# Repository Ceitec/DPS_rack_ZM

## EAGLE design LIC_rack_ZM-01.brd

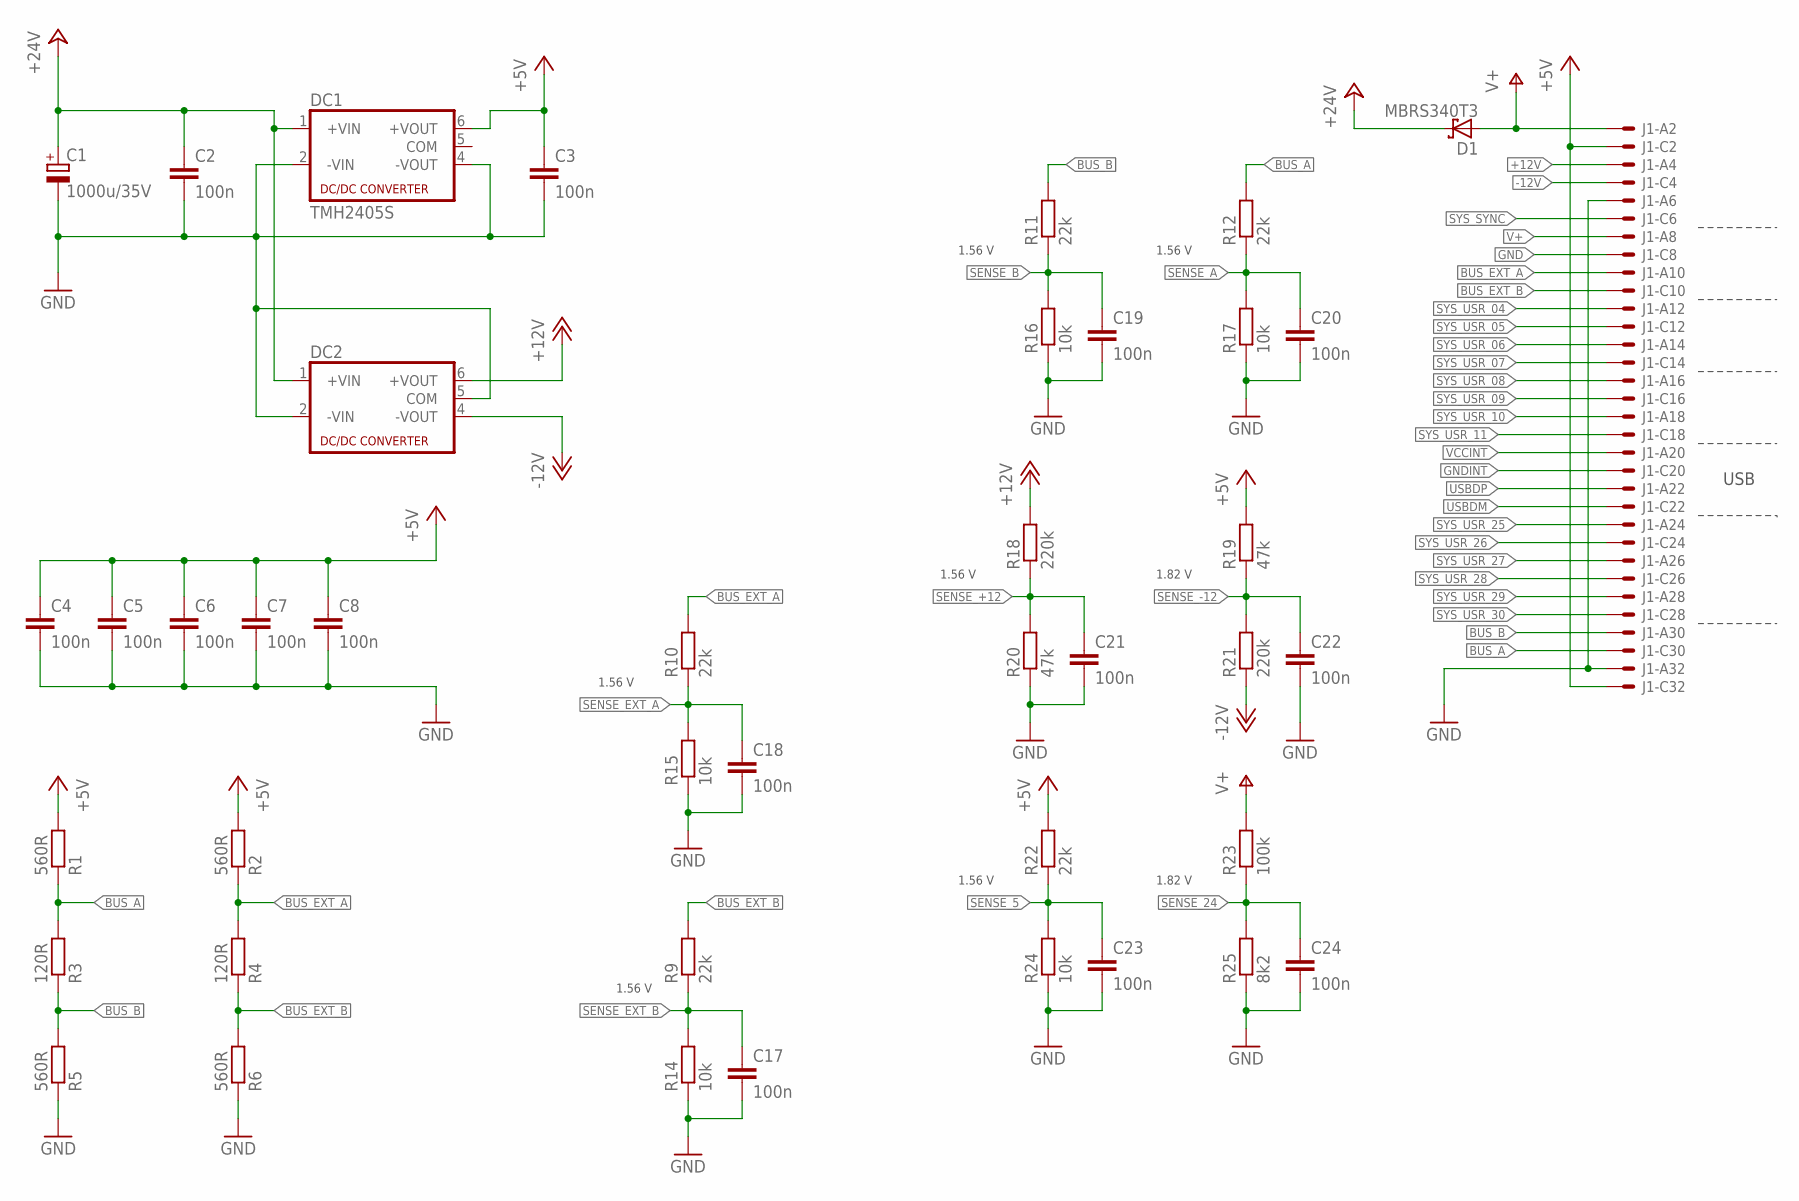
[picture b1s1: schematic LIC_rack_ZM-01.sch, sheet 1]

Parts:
C1: 1000u/35V; E5-13X26-LR
C2, C3, C4, C5, C6, C7, C8, C17, C18, C19, C20, C21, C22, C23, C24: 100n; C1206
D1: MBRS340T3; SMC
DC1: TMH2405S; NMA
DC2: NMA
J1: VG32SP; VG32P
R1, R2, R5, R6: 560R; R1206
R3, R4: 120R; R1206
R9, R10, R11, R12, R22: 22k; R1206
R14, R15, R16, R17, R24: 10k; R1206
R18, R21: 220k; R1206
R19, R20: 47k; R1206
R23: 100k; R1206
R25: 8k2; R1206

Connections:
+5V: C3.1, C4.1, C5.1, C6.1, C7.1, C8.1, DC1.6 (+VOUT), J1.C2 (MS), J1.C32 (MSV), R1.2, R2.2, R19.2, R22.2; also elsewhere on the board
+12V: DC2.6 (+VOUT), J1.A4 (MS), R18.2
+24V: C1.+, C2.1, D1.C, DC1.1 (+VIN), DC2.1 (+VIN)
-12V: DC2.4 (-VOUT), J1.C4 (MS), R21.1
BUS_A: J1.C30 (MS), R1.1, R3.2, R12.2; also elsewhere on the board
BUS_B: J1.A30 (MS), R3.1, R5.2, R11.2; also elsewhere on the board
BUS_EXT_A: J1.A10 (MS), R2.1, R4.2, R10.2; also elsewhere on the board
BUS_EXT_B: J1.C10 (MS), R4.1, R6.2, R9.2; also elsewhere on the board
GND: C1.-, C2.2, C3.2, C4.2, C5.2, C6.2, C7.2, C8.2, C17.2, C18.2, C19.2, C20.2, C21.2, C22.2, C23.2, C24.2, DC1.2 (-VIN), DC1.4 (-VOUT), DC2.2 (-VIN), DC2.5 (COM), J1.A6 (MS), J1.A32 (MS), J1.C8 (MS), R5.1, R6.1, R14.1, R15.1, R16.1, R17.1, R20.1, R24.1, R25.1; also elsewhere on the board
GNDINT: J1.C20 (MS); also elsewhere on the board
SENSE_5: C23.1, R22.1, R24.2; also elsewhere on the board
SENSE_24: C24.1, R23.1, R25.2; also elsewhere on the board
SENSE_+12: C21.1, R18.1, R20.2; also elsewhere on the board
SENSE_-12: C22.1, R19.1, R21.2; also elsewhere on the board
SENSE_A: C20.1, R12.1, R17.2; also elsewhere on the board
SENSE_B: C19.1, R11.1, R16.2; also elsewhere on the board
SENSE_EXT_A: C18.1, R10.1, R15.2; also elsewhere on the board
SENSE_EXT_B: C17.1, R9.1, R14.2; also elsewhere on the board
SYS_SYNC: J1.C6 (MS)
SYS_USR_04: J1.A12 (MS)
SYS_USR_05: J1.C12 (MS)
SYS_USR_06: J1.A14 (MS)
SYS_USR_07: J1.C14 (MS)
SYS_USR_08: J1.A16 (MS)
SYS_USR_09: J1.C16 (MS)
SYS_USR_10: J1.A18 (MS)
SYS_USR_11: J1.C18 (MS)
SYS_USR_25: J1.A24 (MS)
SYS_USR_26: J1.C24 (MS)
SYS_USR_27: J1.A26 (MS)
SYS_USR_28: J1.C26 (MS)
SYS_USR_29: J1.A28 (MS)
SYS_USR_30: J1.C28 (MS)
USBDM: J1.C22 (MS); also elsewhere on the board
USBDP: J1.A22 (MS); also elsewhere on the board
V+: D1.A, J1.A2 (MS), J1.A8 (MS), R23.2
VCCINT: J1.A20 (MS); also elsewhere on the board

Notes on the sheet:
1.82 V
1.56 V
USB

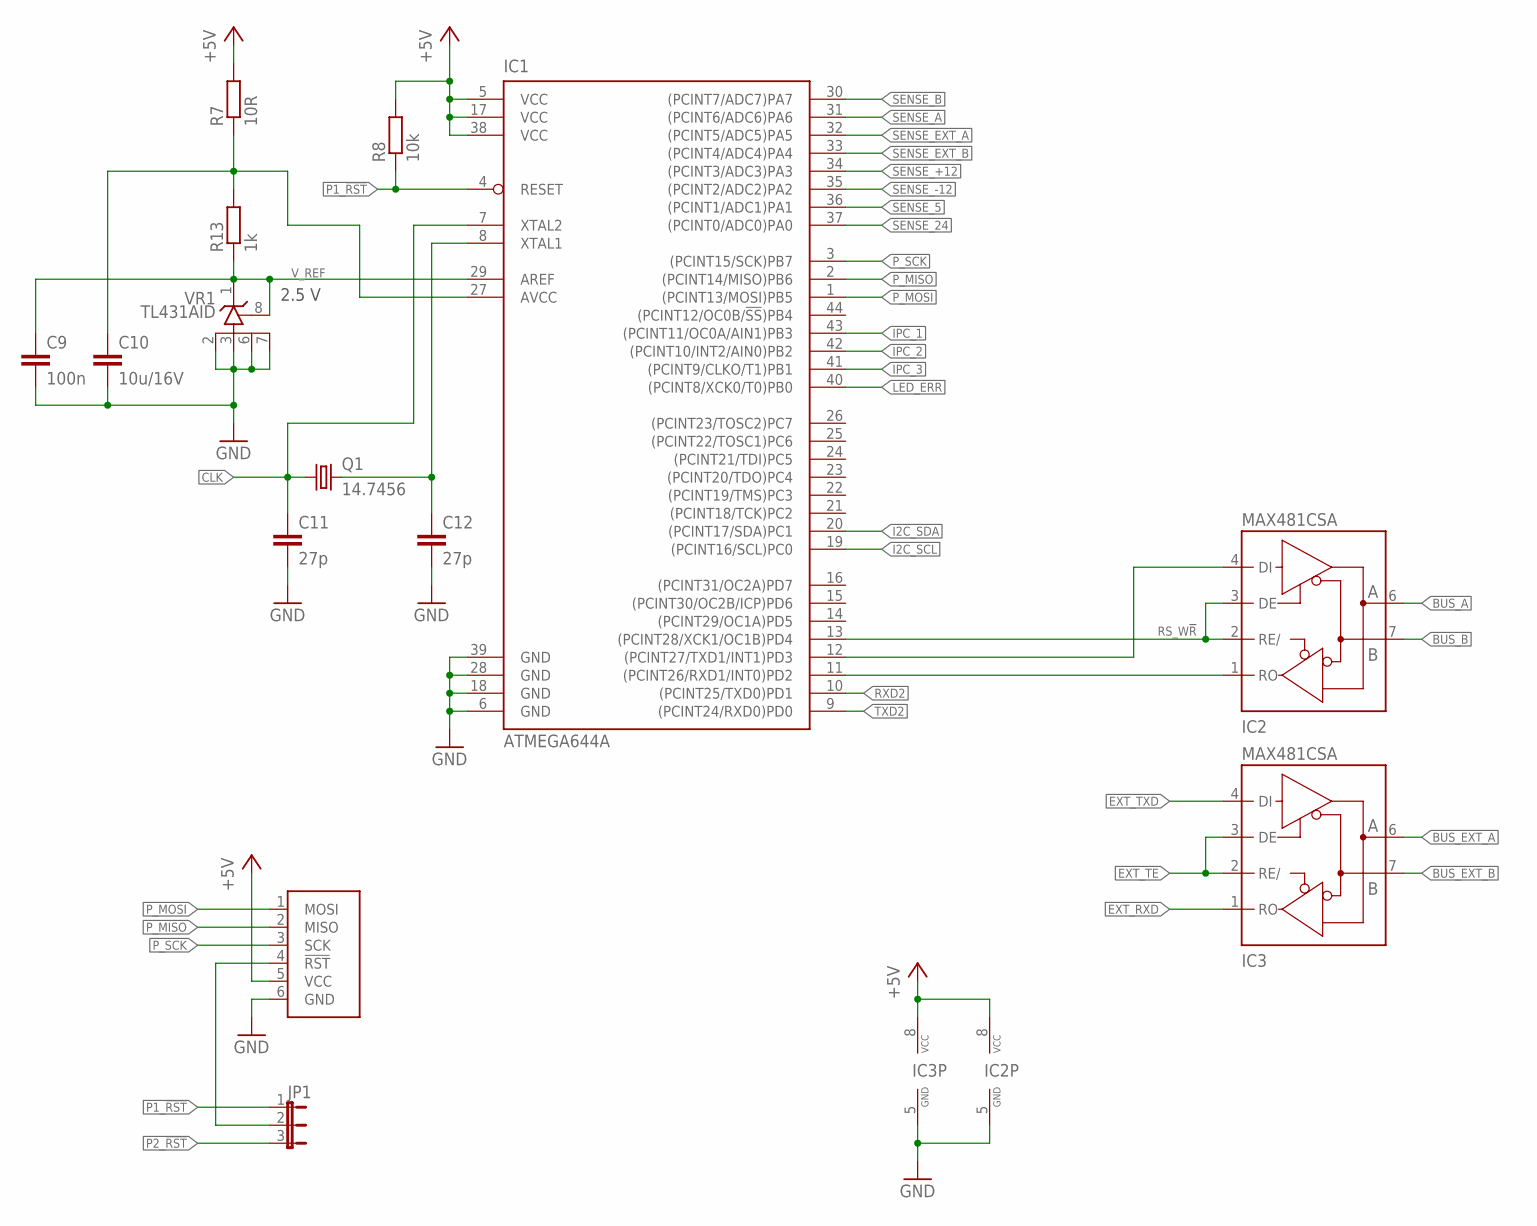
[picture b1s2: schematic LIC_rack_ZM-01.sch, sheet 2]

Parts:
C9: 100n; C1206
C10: 10u/16V; C1206
C11, C12: 27p; C0805
IC1: ATMEGA644A; TQFP44
IC2, IC3: MAX481CSA; SO08
JP1: JP2E; JP2
Q1: 14.7456; HC49U70
R7: 10R; R1206
R8: 10k; R1206
R13: 1k; R1206
U1: ATPROG-V; 6410-06
VR1: TL431AID; SO-08

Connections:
!RST: JP1.2, U1.4 (!RST)
+5V: IC1.5 (VCC), IC1.17 (VCC), IC1.38 (VCC), IC2.8 (VCC), IC3.8 (VCC), R7.2, R8.2, U1.5 (VCC); also elsewhere on the board
+5V_AD: C10.1, IC1.27 (AVCC), R7.1, R13.2
BUS_A: IC2.6 (A); also elsewhere on the board
BUS_B: IC2.7 (B); also elsewhere on the board
BUS_EXT_A: IC3.6 (A); also elsewhere on the board
BUS_EXT_B: IC3.7 (B); also elsewhere on the board
CLK: C11.1, IC1.7 (XTAL2), Q1.1; also elsewhere on the board
EXT_RXD: IC3.1 (RO); also elsewhere on the board
EXT_TE: IC3.2 (RE/), IC3.3 (DE); also elsewhere on the board
EXT_TXD: IC3.4 (DI); also elsewhere on the board
GND: C9.2, C10.2, C11.2, C12.2, IC1.6 (GND), IC1.18 (GND), IC1.28 (GND), IC1.39 (GND), IC2.5 (GND), IC3.5 (GND), U1.6 (GND), VR1.2 (A3), VR1.3 (A2), VR1.6 (A1), VR1.7 (A); also elsewhere on the board
I2C_SCL: IC1.19 ((PCINT16/SCL)PC0); also elsewhere on the board
I2C_SDA: IC1.20 ((PCINT17/SDA)PC1); also elsewhere on the board
IPC_1: IC1.43 ((PCINT11/OC0A/AIN1)PB3); also elsewhere on the board
IPC_2: IC1.42 ((PCINT10/INT2/AIN0)PB2); also elsewhere on the board
IPC_3: IC1.41 ((PCINT9/CLKO/T1)PB1); also elsewhere on the board
LED_ERR: IC1.40 ((PCINT8/XCK0/T0)PB0); also elsewhere on the board
unnamed: C12.1, IC1.8 (XTAL1), Q1.2
P1_!RST: IC1.4 (RESET), JP1.1, R8.1
P2_!RST: JP1.3; also elsewhere on the board
P_MISO: IC1.2 ((PCINT14/MISO)PB6), U1.2 (MISO); also elsewhere on the board
P_MOSI: IC1.1 ((PCINT13/MOSI)PB5), U1.1 (MOSI); also elsewhere on the board
P_SCK: IC1.3 ((PCINT15/SCK)PB7), U1.3 (SCK); also elsewhere on the board
RS_RXD: IC1.11 ((PCINT26/RXD1/INT0)PD2), IC2.1 (RO)
RS_TXD: IC1.12 ((PCINT27/TXD1/INT1)PD3), IC2.4 (DI)
RS_W!R!: IC1.13 ((PCINT28/XCK1/OC1B)PD4), IC2.2 (RE/), IC2.3 (DE)
RXD2: IC1.10 ((PCINT25/TXD0)PD1); also elsewhere on the board
SENSE_5: IC1.36 ((PCINT1/ADC1)PA1); also elsewhere on the board
SENSE_24: IC1.37 ((PCINT0/ADC0)PA0); also elsewhere on the board
SENSE_+12: IC1.34 ((PCINT3/ADC3)PA3); also elsewhere on the board
SENSE_-12: IC1.35 ((PCINT2/ADC2)PA2); also elsewhere on the board
SENSE_A: IC1.31 ((PCINT6/ADC6)PA6); also elsewhere on the board
SENSE_B: IC1.30 ((PCINT7/ADC7)PA7); also elsewhere on the board
SENSE_EXT_A: IC1.32 ((PCINT5/ADC5)PA5); also elsewhere on the board
SENSE_EXT_B: IC1.33 ((PCINT4/ADC4)PA4); also elsewhere on the board
TXD2: IC1.9 ((PCINT24/RXD0)PD0); also elsewhere on the board
V_REF: C9.1, IC1.29 (AREF), R13.1, VR1.1 (C), VR1.8 (R)

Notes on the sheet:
2.5 V

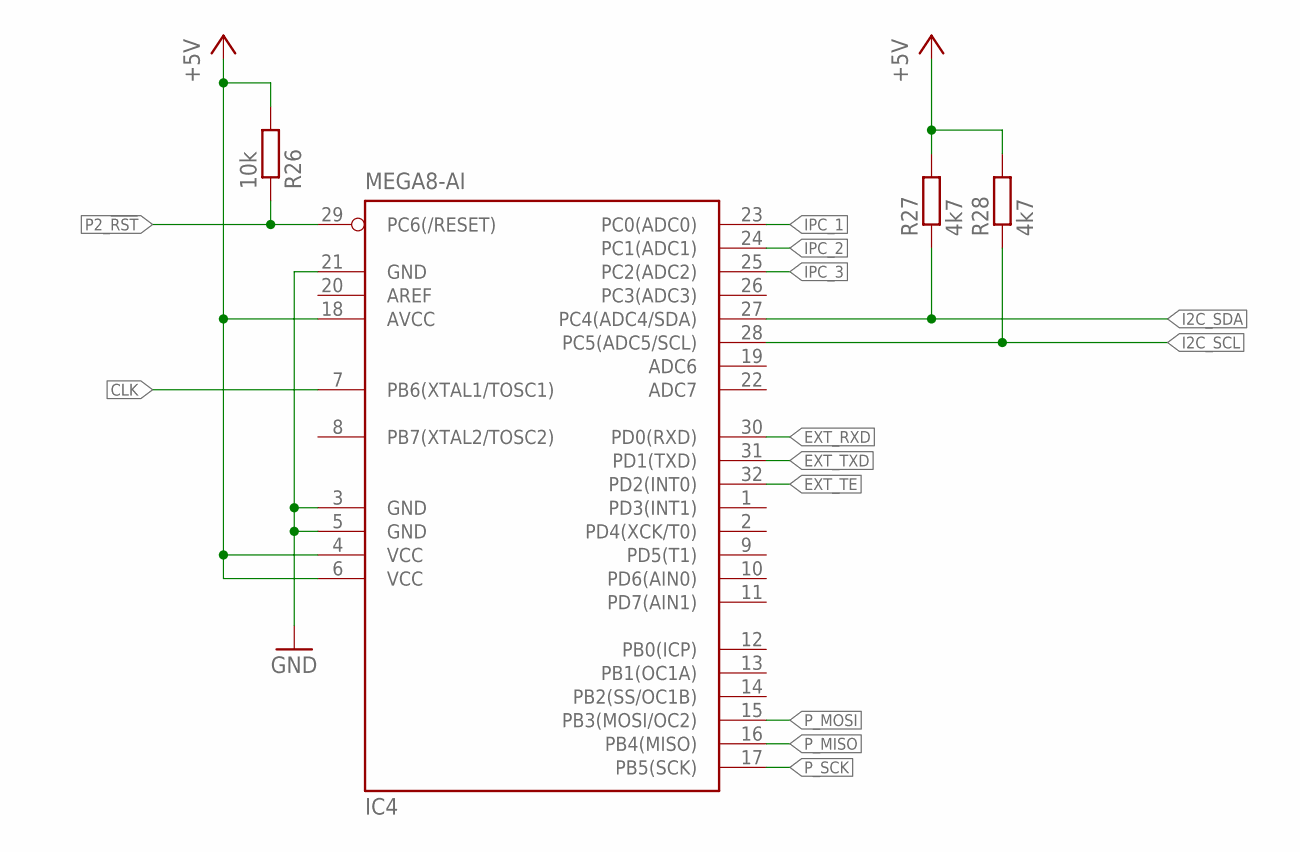
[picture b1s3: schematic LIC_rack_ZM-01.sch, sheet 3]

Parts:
IC4: MEGA8-AI; TQFP32-08
R26: 10k; R1206
R27, R28: 4k7; R1206

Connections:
+5V: IC4.4 (VCC), IC4.6 (VCC), IC4.18 (AVCC), R26.2, R27.2, R28.2; also elsewhere on the board
CLK: IC4.7 (PB6(XTAL1/TOSC1)); also elsewhere on the board
EXT_RXD: IC4.30 (PD0(RXD)); also elsewhere on the board
EXT_TE: IC4.32 (PD2(INT0)); also elsewhere on the board
EXT_TXD: IC4.31 (PD1(TXD)); also elsewhere on the board
GND: IC4.3 (GND), IC4.5 (GND), IC4.21 (GND); also elsewhere on the board
I2C_SCL: IC4.28 (PC5(ADC5/SCL)), R28.1; also elsewhere on the board
I2C_SDA: IC4.27 (PC4(ADC4/SDA)), R27.1; also elsewhere on the board
IPC_1: IC4.23 (PC0(ADC0)); also elsewhere on the board
IPC_2: IC4.24 (PC1(ADC1)); also elsewhere on the board
IPC_3: IC4.25 (PC2(ADC2)); also elsewhere on the board
P2_!RST: IC4.29 (PC6(/RESET)), R26.1; also elsewhere on the board
P_MISO: IC4.16 (PB4(MISO)); also elsewhere on the board
P_MOSI: IC4.15 (PB3(MOSI/OC2)); also elsewhere on the board
P_SCK: IC4.17 (PB5(SCK)); also elsewhere on the board

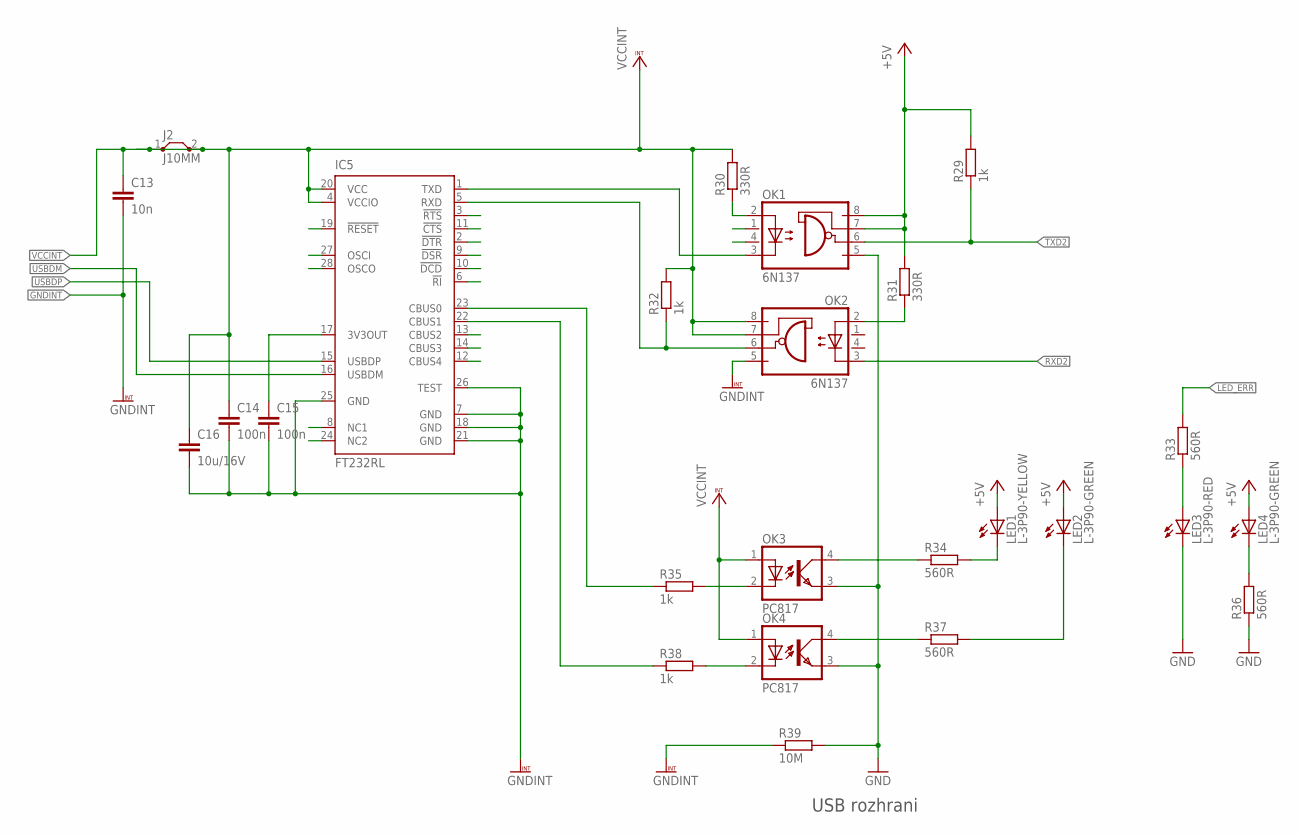
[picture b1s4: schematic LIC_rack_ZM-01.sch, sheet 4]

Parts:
C13: 10n; C0805
C14, C15: 100n; C1206
C16: 10u/16V; C1206
IC5: FT232RL; SSOP28
J2: J10MM; 10
LED1: L-3P90-YELLOW; L-3P90
LED2, LED4: L-3P90-GREEN; L-3P90
LED3: L-3P90-RED; L-3P90
OK1, OK2: 6N137; DIL08
OK3, OK4: PC817; DIL04
R29, R32, R35, R38: 1k; R1206
R30, R31: 330R; R1206
R33, R34, R36, R37: 560R; R1206
R39: 10M; R1206

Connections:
3V3: C15.1, IC5.17 (3V3OUT)
+5V: LED1.A, LED2.A, LED4.A, OK1.7 (VE), OK1.8 (VCC), R29.2, R31.2; also elsewhere on the board
GND: LED3.K (C), OK1.5 (GND), OK3.3 (EMIT), OK4.3 (EMIT), R36.1, R39.2; also elsewhere on the board
GNDINT: C13.2, C14.2, C15.2, C16.2, IC5.7 (GND), IC5.18 (GND), IC5.21 (GND), IC5.25 (GND), IC5.26 (TEST), OK2.5 (GND), R39.1; also elsewhere on the board
LED_ERR: R33.2; also elsewhere on the board
unnamed: LED4.K (C), R36.2
unnamed: IC5.22 (CBUS1), R38.1
unnamed: OK4.2 (C), R38.2
unnamed: OK3.2 (C), R35.2
unnamed: LED3.A, R33.1
unnamed: OK2.2 (A), R31.1
unnamed: OK4.4 (COL), R37.1
unnamed: LED2.K (C), R37.2
unnamed: OK1.2 (A), R30.1
unnamed: OK3.4 (COL), R34.1
unnamed: IC5.23 (CBUS0), R35.1
unnamed: LED1.K (C), R34.2
RXD1: IC5.5 (RXD), OK2.6 (VO), R32.1
RXD2: OK2.3 (C); also elsewhere on the board
TXD1: IC5.1 (TXD), OK1.3 (C)
TXD2: OK1.6 (VO), R29.1; also elsewhere on the board
USBDM: IC5.16 (USBDM); also elsewhere on the board
USBDP: IC5.15 (USBDP); also elsewhere on the board
VCCINT: C13.1, C14.1, C16.1, IC5.4 (VCCIO), IC5.20 (VCC), J2.1, J2.2, OK2.7 (VE), OK2.8 (VCC), OK3.1 (A), OK4.1 (A), R30.2, R32.2; also elsewhere on the board

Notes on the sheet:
USB rozhrani

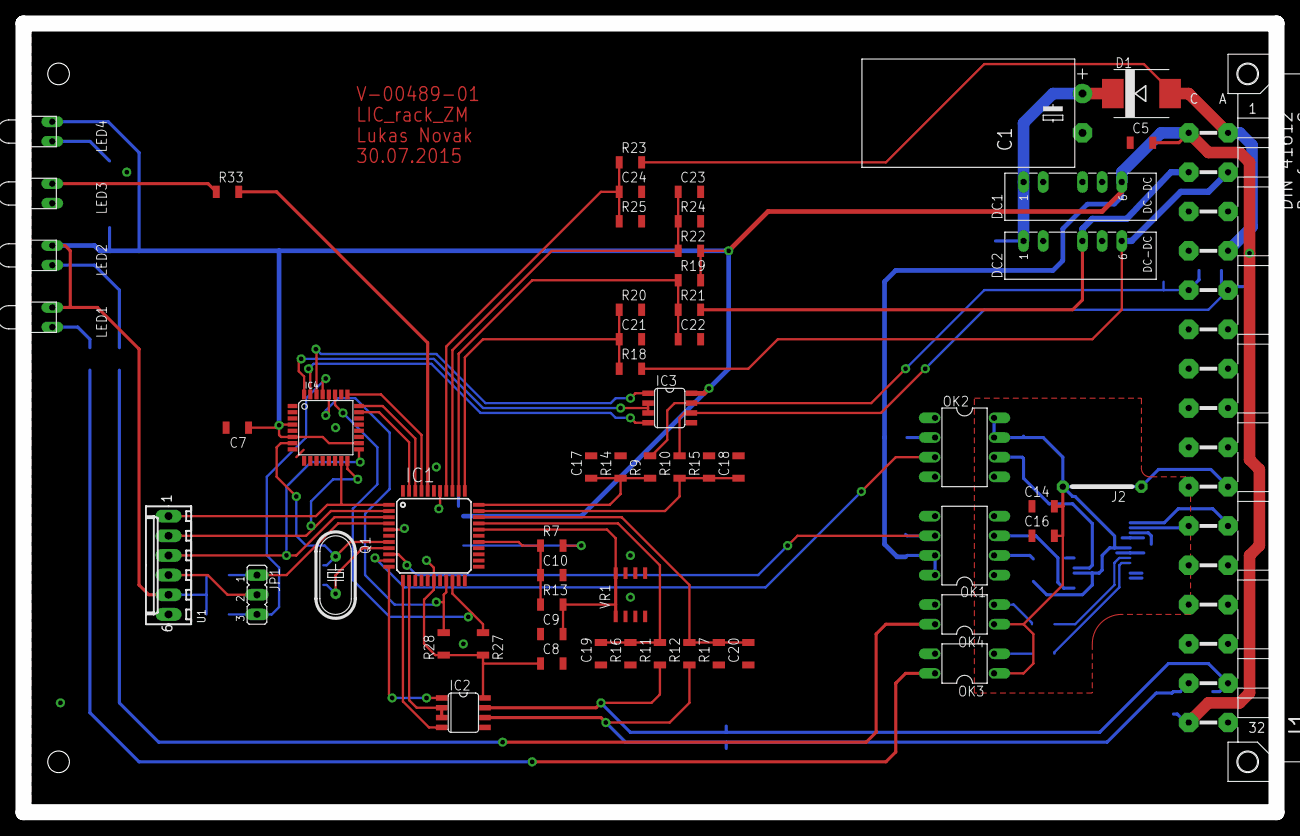
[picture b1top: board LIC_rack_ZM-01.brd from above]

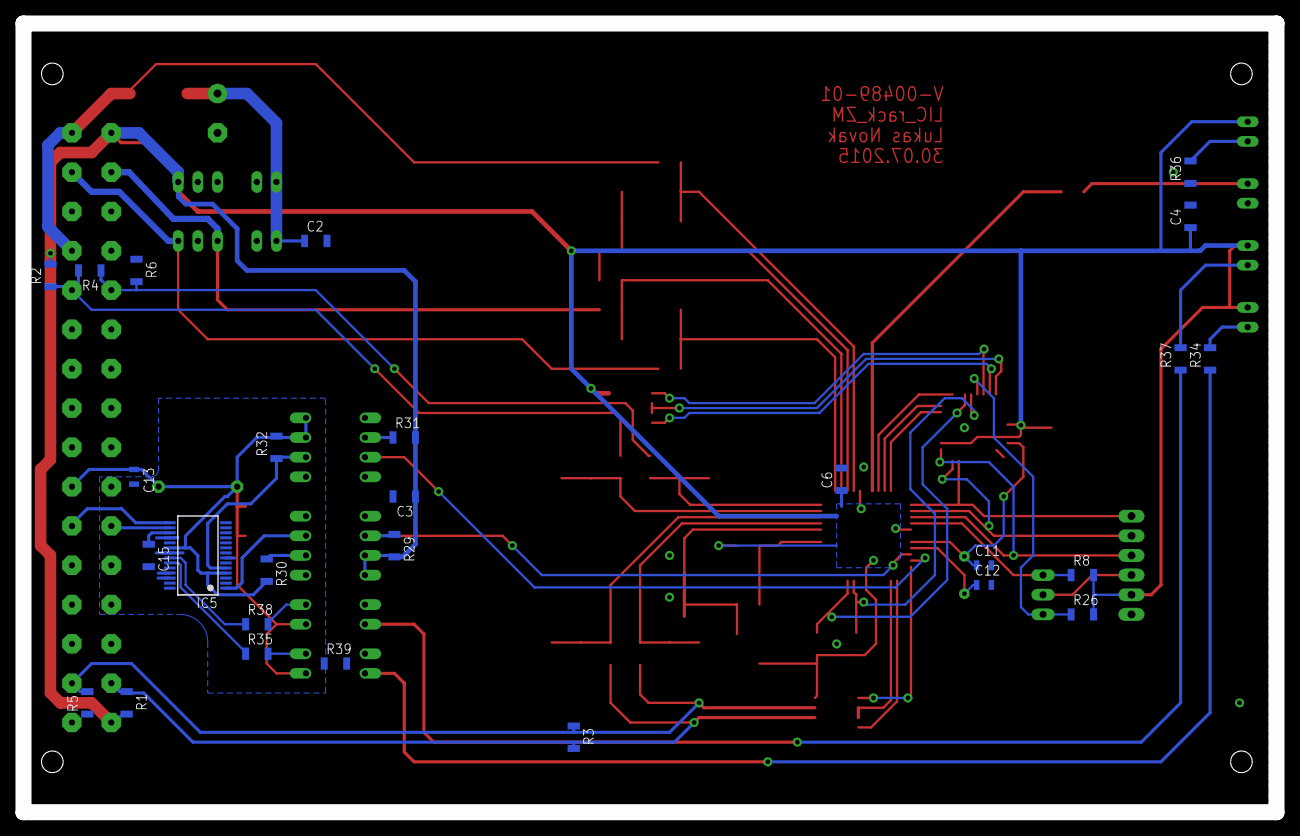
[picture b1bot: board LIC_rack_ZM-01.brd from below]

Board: 2 copper layers, 162.0 x 102.0 mm, 85 parts (27 on the bottom side), 61 nets.

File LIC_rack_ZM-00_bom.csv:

Qty	Value	Device	Parts	GM	code
1		JP2E	JP1		
1		NMA	DC2		
1		VG32SP	J1		
5	1k	R-EU_R1206	R13, R29, R32, R35, R38	R1206 1K	-
1	2k	R-EU_R1206	R37		
3	2k2	R-EU_R1206	R33, R34, R36	R1206 2k2	900-197
2	4k7	R-EU_R1206	R27, R28	R1206 4K7 1%	900-248
2	6N137	6N137	OK1, OK2	6N137	523-009
1	8k2	R-EU_R1206	R25		
1	10M	R-EU_R1206	R39		
1	10R	R-EU_R1206	R7		
7	10k	R-EU_R1206	R8, R14, R15, R16, R17, R24, R26	R1206 10K 1%	900-179
1	10n	C-EUC0805	C13	CK 0805 10nF	-
2	10u/16V	C-EUC1206	C10, C16		
1	14.7456	XTAL	Q1		
5	22k	R-EU_R1206	R9, R10, R11, R12, R22	R1206 22K 1%	900-224
2	27p	C-EUC0805	C11, C12		
2	47k	R-EU_R1206	R19, R20	R1206 47K 1%	900-116
1	100k	R-EU_R1206	R23	R1206 100K 1%	900-002
18	100n	C-EUC1206	C2, C3, C4, C5, C6, C7, C8, C9, C14, C15, C17, C18, C19, C20, C21, C22, C23, C24	CK 1206 100nF	-
2	120R	R-EU_R1206	R3, R4	R1206 120R 1%	900-232
2	220k	R-EU_R1206	R18, R21	R1206 220k	900-275
2	330R	R-EU_R1206	R30, R31	R1206 330R 1%	900-310
4	560R	R-EU_R1206	R1, R2, R5, R6	R1206 560R 1%	900-202
1	1000u/35V	CPOL-EUE5-13X26-LR	C1		
1	ATMEGA644A	ATMEGA644A	IC1		
1	ATPROG-V	ATPROG-V	U1		
1	FT232RL	FT232RL	IC5	FT232RL	-
1	J10MM	J10MM	J2		
2	L-3P90-GREEN	L-3P90-GREEN	LED2, LED4	L-3P90-GREEN	511-347
1	L-3P90-RED	L-3P90-RED	LED3		
1	L-3P90-YELLOW	L-3P90-YELLOW	LED1	L-3P90-YELLOW	511-348
2	MAX481CSA	MAX481CSA	IC2, IC3	75176 SMD	959-001
1	MBRS340T3	MBRS340T3	D1	MBRS340T3	920-099
1	MEGA8-AI	MEGA8-AI	IC4	ATmega8-16AU	958-102
2	PC817	PC817	OK3, OK4	PC817	523-052
1	TL431AID	TL431-SMD	VR1		
1	TMH2405S	NMA	DC1

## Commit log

2015-08-11 :circus_tent: Added .gitattributes & .gitignore files
2015-08-11 Základní deska
2015-09-25 A
    A
2015-11-22 Změna gridu
